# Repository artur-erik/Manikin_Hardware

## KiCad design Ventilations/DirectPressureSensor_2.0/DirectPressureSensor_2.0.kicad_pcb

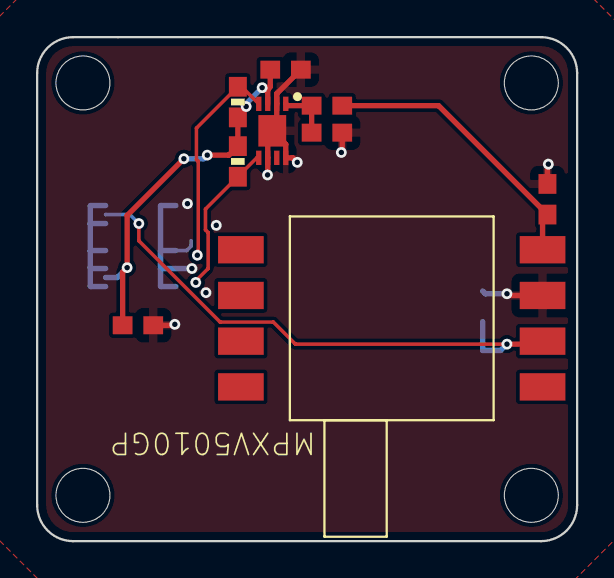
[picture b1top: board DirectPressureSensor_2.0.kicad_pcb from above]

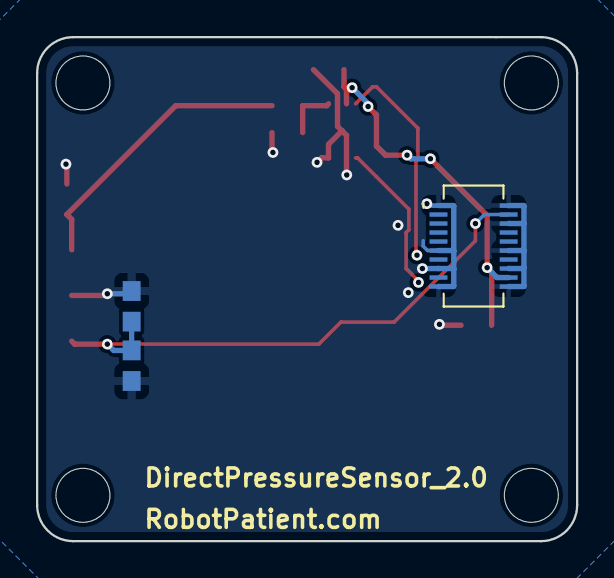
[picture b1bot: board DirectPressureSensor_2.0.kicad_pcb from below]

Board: 2 copper layers, 30.0 x 28.0 mm, 13 parts (3 on the bottom side), 7 nets.

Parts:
C1: 0.1uF; 0603_510
C2: 10uF; 0603_510
C3: 1.0uF; 0603_510
C4: 10nF; 0603_510
C5: 470pF; 0603_510
IC2: MCP3426A0-E_MC; SON50P300X200X100-9N
J5: 658511223020; J_Wurth_WR-BTB_658511223020
R1: 10K 0.1%; 0603_510
R2: 15K 0.1%; 0603_510
R28, R29: 4.7K; 0603-RES
U$3: MPXV5010GP; PRESSURE_SENSOR
U$40: ROBOTPATIENT_SMALL_MODULEBOARD; RP_SMALL_SENSOR_OUTLINE

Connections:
3.3V: C1.1, C2.1, IC2.3 (VDD), J5.19, R28.2, R29.2
5V: C3.2, C4.2, J5.12, U$3.2 (VS)
/Microcontroller/SCL: IC2.5 (SCL), R29.1
/Microcontroller/SDA: IC2.4 (SDA), R28.1
A0_PRESSURE_3.3V: IC2.1 (CH1+), R1.1, R2.2
A0_PRESSURE_5V: C5.2, R1.2, U$3.4 (VOUT)
GND: C1.2, C2.2, C3.1, C4.1, C5.1, IC2.2 (CH1-), IC2.6 (VSS), IC2.8 (CH2-), IC2.9 (EP), J5.1, J5.6, J5.8, J5.10, J5.11, J5.13, J5.16, J5.18, J5.20, R2.1, U$3.3 (GND)

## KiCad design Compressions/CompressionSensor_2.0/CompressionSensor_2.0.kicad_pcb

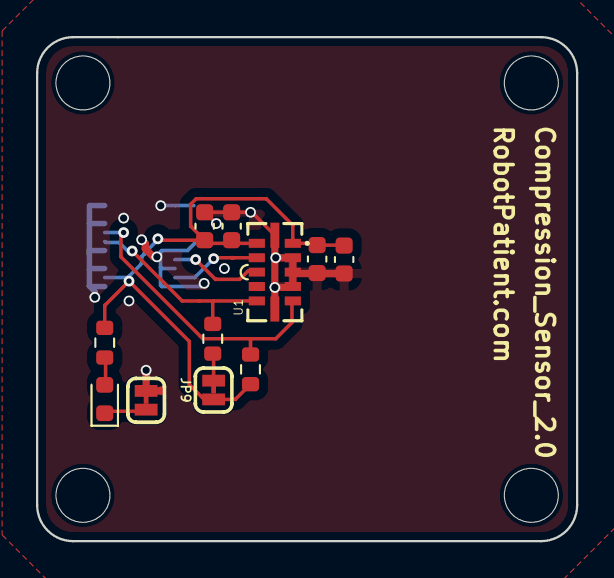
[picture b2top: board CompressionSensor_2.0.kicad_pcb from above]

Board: 2 copper layers, 30.0 x 28.0 mm, 13 parts (1 on the bottom side), 5 nets.

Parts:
C1: 4.7uF; C_0603_1608Metric
C2, C3: 10uF; C_0603_1608Metric
C4: 0.1uF; C_0603_1608Metric
D2: LED; LED_0603_1608Metric
J5: 658511223020; J_Wurth_WR-BTB_658511223020
JP9: INT; SMT-JUMPER_2_NC_TRACE_SILK
PWR0: INT; SMT-JUMPER_2_NC_TRACE_SILK
R1, R2: 10k; R_0603_1608Metric
R3: 1k; R_0603_1608Metric
U1: VL53L4CD
U$40: ROBOTPATIENT_SMALL_MODULEBOARD; RP_SMALL_SENSOR_OUTLINE

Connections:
3.3V: C1.1, C2.1, C3.1, C4.1, J5.19, JP9.2, R2.2, R3.2, U1.1, U1.11
/~INT: J5.15, R1.1
/~SHUT: J5.14, R2.1
GND: C1.2, C2.2, C3.2, C4.2, J5.1, J5.6, J5.8, J5.10, J5.11, J5.13, J5.16, J5.18, J5.20, PWR0.1, U1.2, U1.3, U1.4, U1.6, U1.12
unnamed: D2.2 (A), R3.1

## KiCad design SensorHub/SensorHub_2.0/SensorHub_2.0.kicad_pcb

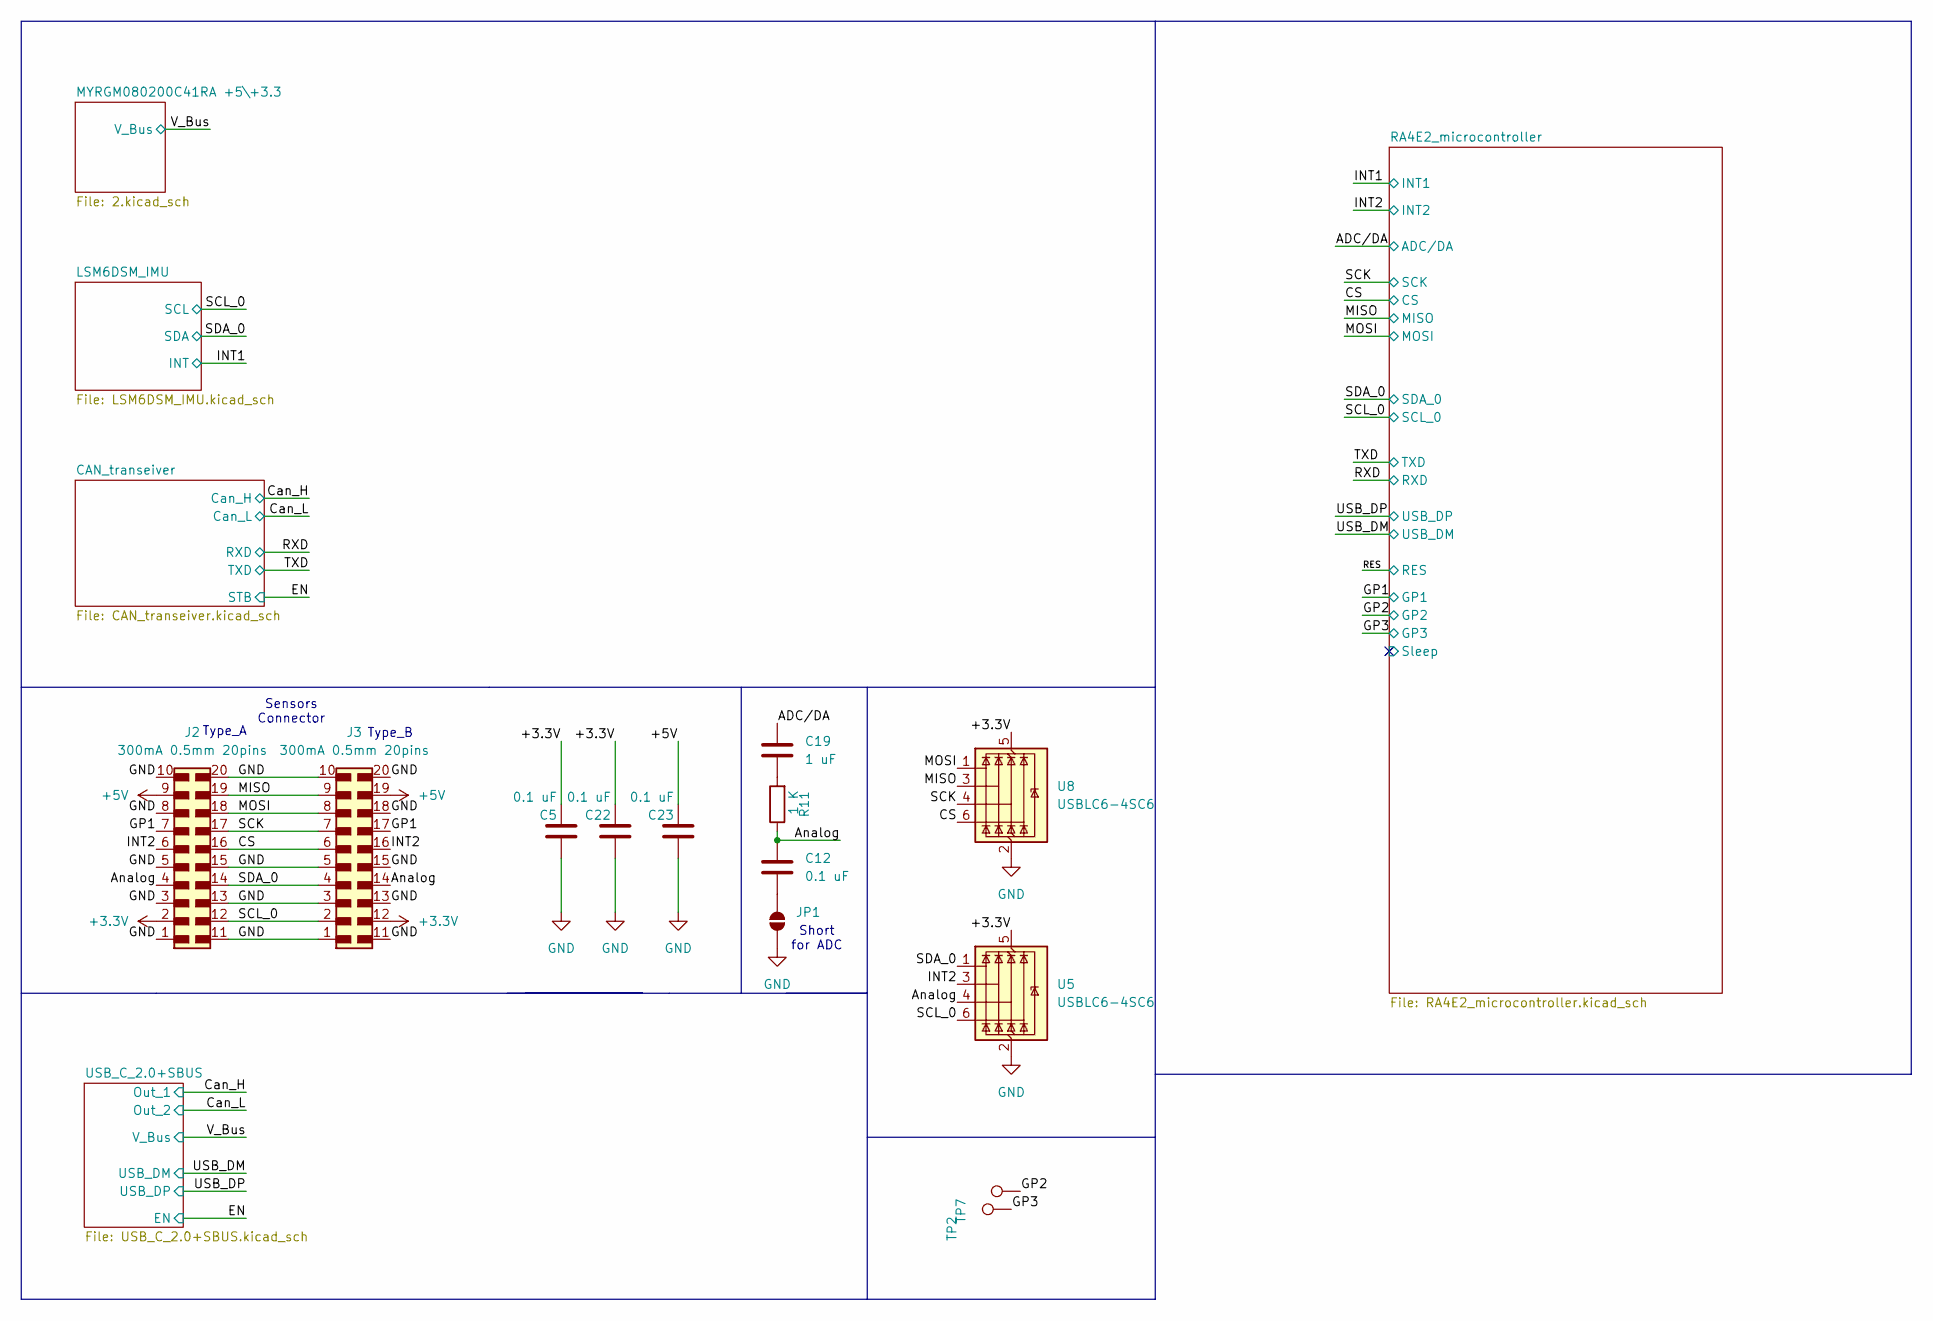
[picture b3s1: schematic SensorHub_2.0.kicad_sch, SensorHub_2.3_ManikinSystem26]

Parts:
C5, C12, C22, C23: 0.1 uF; C_0603_1608Metric
C19: 1 uF; C_0603_1608Metric
J2, J3: 658561423020; J_Wurth_WR-BTB_658561423020; Part Number 658561423020
JP1: SolderJumper_2_Open; SolderJumper-2_P1.3mm_Open_RoundedPad1.0x1.5mm
R11: 1 K; R_0603_1608Metric
TP2, TP7: TestPoint; TestPoint_Pad_1.0x1.0mm
U5, U8: USBLC6-4SC6; SOT-23-6; MPN USBLC6-4SC6Y

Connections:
+3.3V: C5.1, C22.1, J2.2, J3.12, U5.5 (VBUS), U8.5 (VBUS); also elsewhere on the board
+5V: C23.1, J2.9, J3.19; also elsewhere on the board
/ADC/DA: C19.1; also elsewhere on the board
/Analog: C12.1, J2.4, J3.14, R11.1, U5.4 (I/O3)
/CS: J2.16, J3.6, U8.6 (I/O4); also elsewhere on the board
/GP1: J2.7, J3.17; also elsewhere on the board
/GP2: TP7.1; also elsewhere on the board
/GP3: TP2.1; also elsewhere on the board
/INT2: J2.6, J3.16, U5.3 (I/O2); also elsewhere on the board
/MISO: J2.19, J3.9, U8.3 (I/O2); also elsewhere on the board
/MOSI: J2.18, J3.8, U8.1 (I/O1); also elsewhere on the board
/SCK: J2.17, J3.7, U8.4 (I/O3); also elsewhere on the board
/SCL_0: J2.12, J3.2, U5.6 (I/O4); also elsewhere on the board
/SDA_0: J2.14, J3.4, U5.1 (I/O1); also elsewhere on the board
GND: C5.2, C22.2, C23.2, J2.1, J2.3, J2.5, J2.8, J2.10, J2.11, J2.13, J2.15, J2.20, J3.1, J3.3, J3.5, J3.10, J3.11, J3.13, J3.15, J3.18, J3.20, JP1.1 (A), U5.2 (GND), U8.2 (GND); also elsewhere on the board
unnamed: C19.2, R11.2
unnamed: C12.2, JP1.2 (B)

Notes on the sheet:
Type_A
Sensors Connector
Type_B
Short for ADC

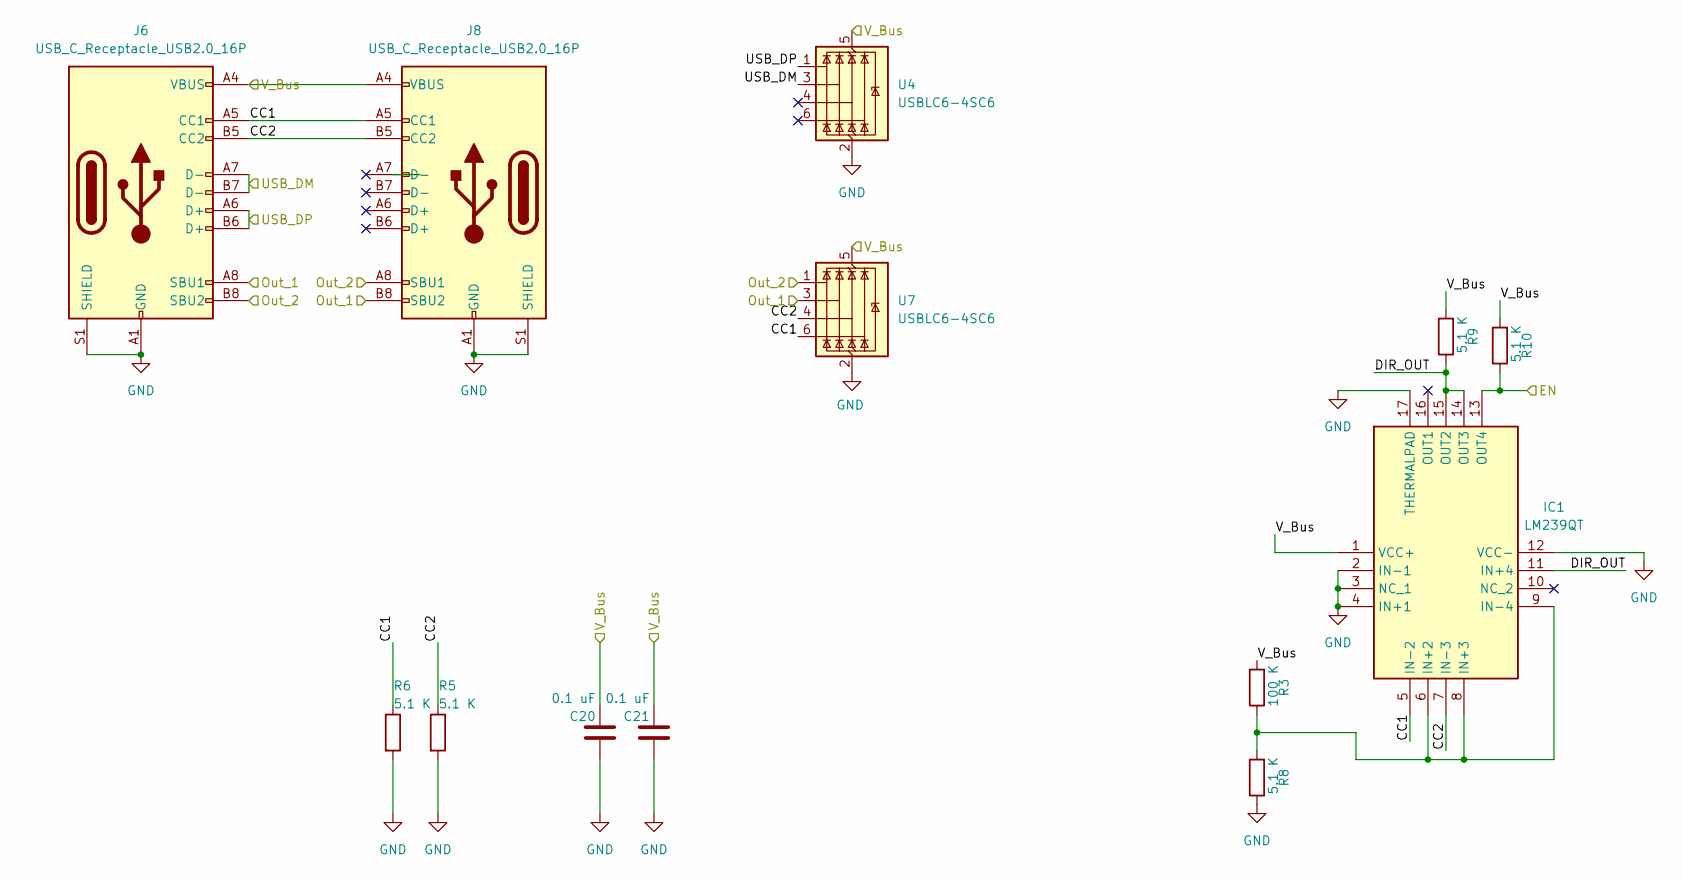
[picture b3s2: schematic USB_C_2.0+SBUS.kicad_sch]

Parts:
C20, C21: 0.1 uF; C_0603_1608Metric
IC1: LM239QT; QFN50P300X300X100-17N; Mouser Part Number 511-LM239QT
J6, J8: USB_C_Receptacle_USB2.0_16P; USB_C_Receptacle_Palconn_UTC16-G
R3: 100 K; R_0603_1608Metric
R5, R6, R8, R9, R10: 5.1 K; R_0603_1608Metric
U4, U7: USBLC6-4SC6; SOT-23-6; MPN USBLC6-4SC6Y

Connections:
/Can_H: J6.A8 (SBU1), J8.B8 (SBU2), U7.3 (I/O2); also elsewhere on the board
/Can_L: J6.B8 (SBU2), J8.A8 (SBU1), U7.1 (I/O1); also elsewhere on the board
/EN: IC1.13 (OUT4), R10.1; also elsewhere on the board
/USB_C_2.0+SBUS/CC1: IC1.5 (IN-2), J6.A5 (CC1), J8.A5 (CC1), R6.1, U7.6 (I/O4)
/USB_C_2.0+SBUS/CC2: IC1.7 (IN-3), J6.B5 (CC2), J8.B5 (CC2), R5.1, U7.4 (I/O3)
/USB_C_2.0+SBUS/DIR_OUT: IC1.11 (IN+4), IC1.14 (OUT3), IC1.15 (OUT2), R9.1
/USB_DM: J6.A7 (D-), J6.B7 (D-), U4.3 (I/O2); also elsewhere on the board
/USB_DP: J6.A6 (D+), J6.B6 (D+), U4.1 (I/O1); also elsewhere on the board
/V_Bus: C20.1, C21.1, IC1.1 (VCC+), J6.A4 (VBUS), J6.A9 (VBUS), J6.B4 (VBUS), J6.B9 (VBUS), J8.A4 (VBUS), J8.A9 (VBUS), J8.B4 (VBUS), J8.B9 (VBUS), R3.2, R9.2, R10.2, U4.5 (VBUS), U7.5 (VBUS); also elsewhere on the board
GND: C20.2, C21.2, IC1.2 (IN-1), IC1.3 (NC_1), IC1.4 (IN+1), IC1.12 (VCC-), IC1.17 (THERMALPAD), J6.A1 (GND), J6.A12 (GND), J6.B1 (GND), J6.B12 (GND), J6.S1 (SHIELD), J8.A1 (GND), J8.A12 (GND), J8.B1 (GND), J8.B12 (GND), J8.S1 (SHIELD), R5.2, R6.2, R8.1, U4.2 (GND), U7.2 (GND); also elsewhere on the board
unnamed: IC1.6 (IN+2), IC1.8 (IN+3), IC1.9 (IN-4), R3.1, R8.2

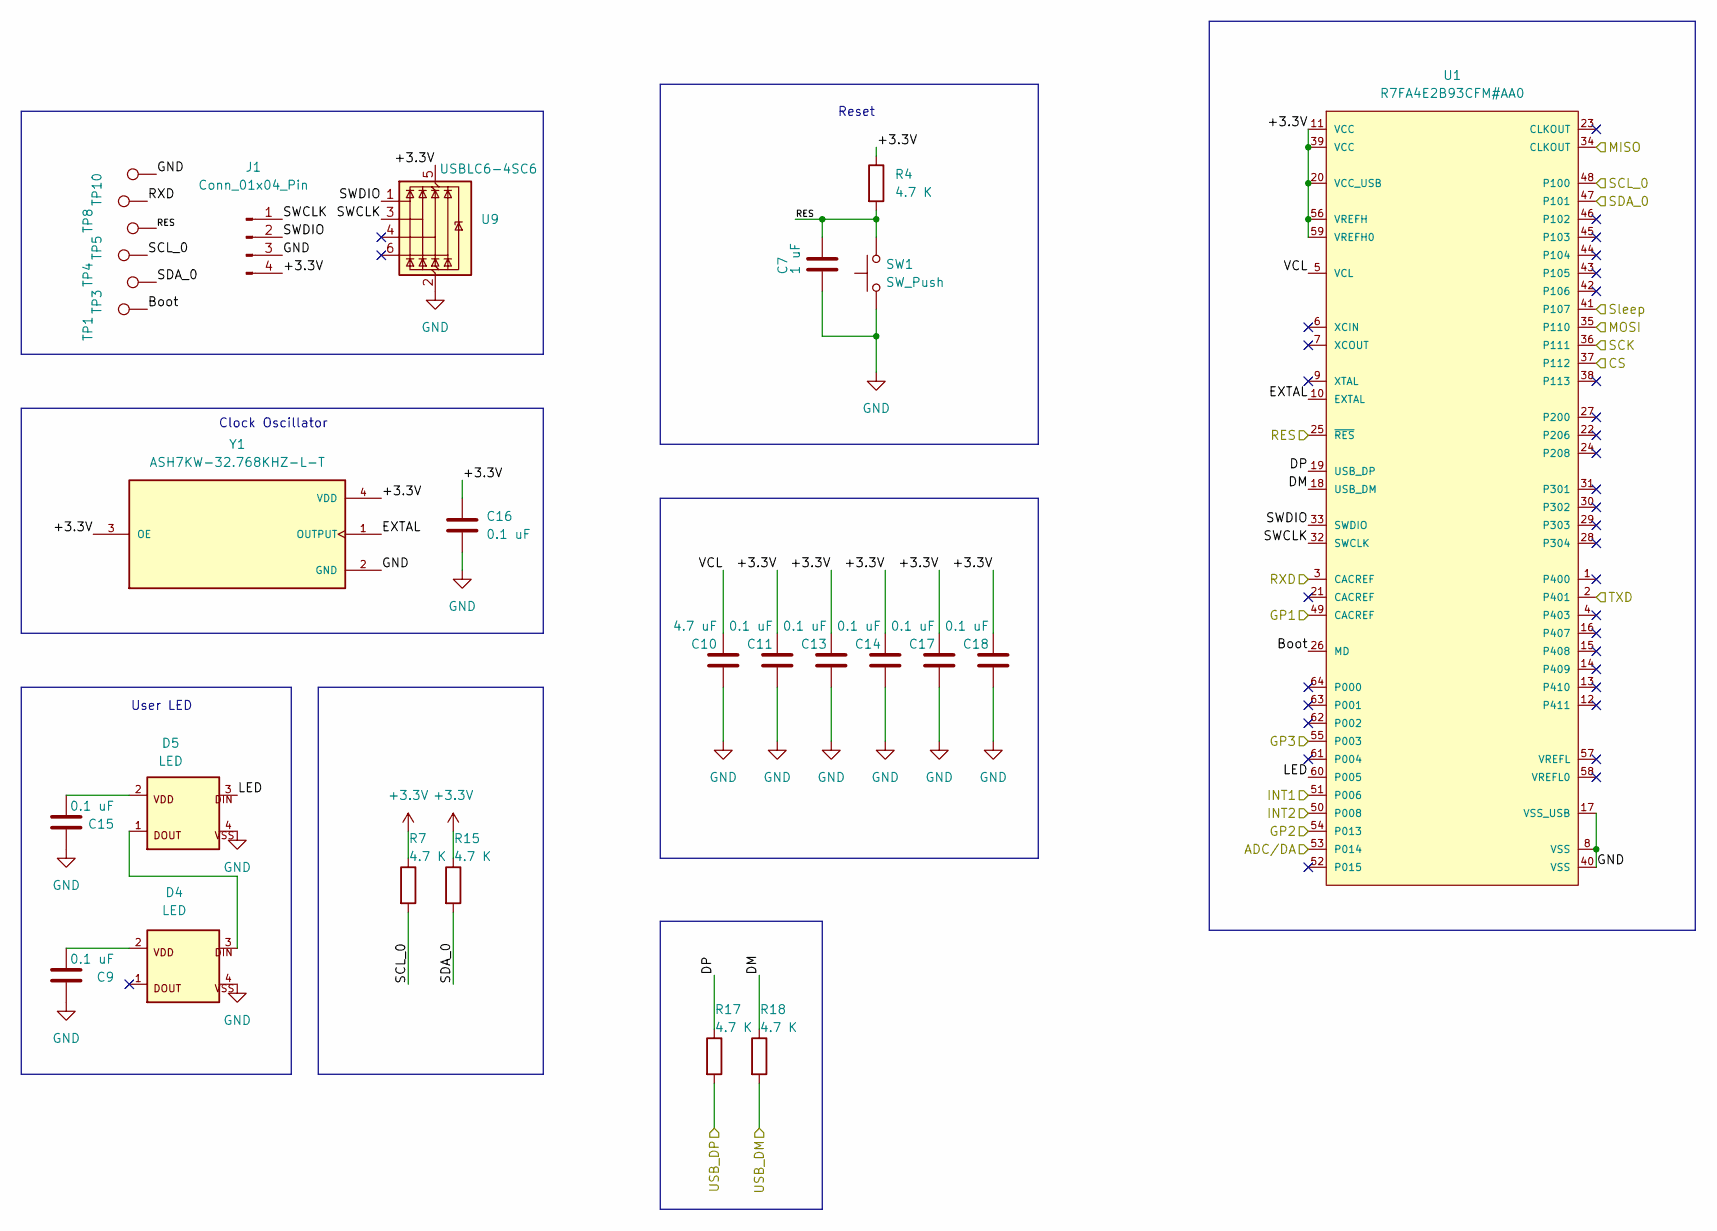
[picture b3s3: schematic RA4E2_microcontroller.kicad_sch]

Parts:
C7: 1 uF; C_0603_1608Metric
C9, C11, C13, C14, C15, C16, C17, C18: 0.1 uF; C_0603_1608Metric
C10: 4.7 uF; C_0603_1608Metric
D4, D5: LED; 1312020030000; MPN 1312020030000
J1: Conn_01x04_Pin; PinHeader_1x04_P1.27mm_Vertical
R4, R7, R15, R17, R18: 4.7 K; R_0603_1608Metric
SW1: SW_Push; B3U-1000P(M)-B; MPN B3U-1000PM-B
TP1, TP3, TP4, TP5, TP8, TP10: TestPoint; TestPoint_Pad_1.0x1.0mm
U1: R7FA4E2B93CFM#AA0; Renesas-PLQP0064KB-C-0-0-IPC_A; MPN R7FA4E2B93CFM#AA0
U9: USBLC6-4SC6; SOT-23-6; MPN USBLC6-4SC6Y
Y1: ASH7KW-32.768KHZ-L-T; XTAL_ASH7KW-32.768KHZ-L-T; PARTREV 07.07.2021

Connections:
+3.3V: C11.1, C13.1, C14.1, C16.1, C17.1, C18.1, J1.4, R4.1, R7.1, R15.1, U1.11 (VCC), U1.20 (VCC_USB), U1.39 (VCC), U1.56 (VREFH), U1.59 (VREFH0), U9.5 (VBUS), Y1.3 (OE), Y1.4 (VDD); also elsewhere on the board
/ADC/DA: U1.53 (P014); also elsewhere on the board
/CS: U1.37 (P112); also elsewhere on the board
/GP1: U1.49 (CACREF); also elsewhere on the board
/GP2: U1.54 (P013); also elsewhere on the board
/GP3: U1.55 (P003); also elsewhere on the board
/INT1: U1.51 (P006); also elsewhere on the board
/INT2: U1.50 (P008); also elsewhere on the board
/MISO: U1.34 (CLKOUT); also elsewhere on the board
/MOSI: U1.35 (P110); also elsewhere on the board
/RA4E2_microcontroller/Boot: TP1.1, U1.26 (MD)
/RA4E2_microcontroller/DM: R18.1, U1.18 (USB_DM)
/RA4E2_microcontroller/DP: R17.1, U1.19 (USB_DP)
/RA4E2_microcontroller/EXTAL: U1.10 (EXTAL), Y1.1 (OUTPUT)
/RA4E2_microcontroller/LED: D5.3, U1.60 (P005)
/RA4E2_microcontroller/SWCLK: J1.1, U1.32 (SWCLK), U9.3 (I/O2)
/RA4E2_microcontroller/SWDIO: J1.2, U1.33 (SWDIO), U9.1 (I/O1)
/RA4E2_microcontroller/Sleep: U1.41 (P107)
/RA4E2_microcontroller/VCL: C10.1, U1.5 (VCL)
/RES: C7.1, R4.2, SW1.2, TP5.1, U1.25 (~RES)
/RXD: TP8.1, U1.3 (CACREF); also elsewhere on the board
/SCK: U1.36 (P111); also elsewhere on the board
/SCL_0: R7.2, TP4.1, U1.48 (P100); also elsewhere on the board
/SDA_0: R15.2, TP3.1, U1.47 (P101); also elsewhere on the board
/TXD: U1.2 (P401); also elsewhere on the board
/USB_DM: R18.2; also elsewhere on the board
/USB_DP: R17.2; also elsewhere on the board
GND: C7.2, C9.2, C10.2, C11.2, C13.2, C14.2, C15.2, C16.2, C17.2, C18.2, D4.4, D5.4, J1.3, SW1.1, TP10.1, U1.8 (VSS), U1.17 (VSS_USB), U1.40 (VSS), U9.2 (GND), Y1.2 (GND); also elsewhere on the board
unnamed: C9.1, D4.2
unnamed: C15.1, D5.2
unnamed: D4.3, D5.1

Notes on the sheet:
User LED
Clock Oscillator
Reset

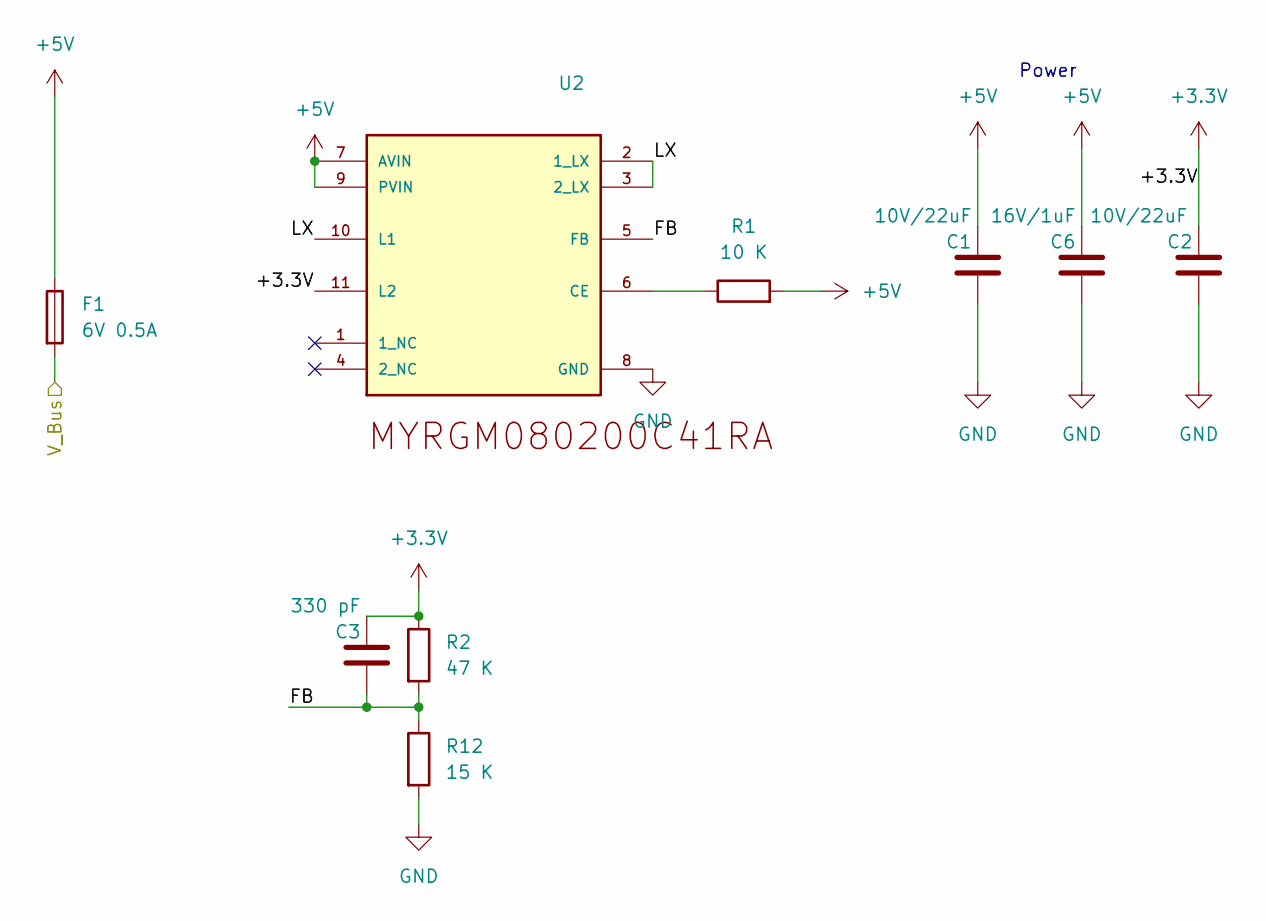
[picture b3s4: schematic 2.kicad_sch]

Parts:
C1, C2: 10V/22uF; C_0603_1608Metric
C3: 330 pF; C_0603_1608Metric
C6: 16V/1uF; C_0603_1608Metric
F1: 6V 0.5A; Fuse_1206_3216Metric_Pad1.42x1.75mm_HandSolder; MPN SMD1206B050TF
R1: 10 K; R_0603_1608Metric
R2: 47 K; R_0603_1608Metric
R12: 15 K; R_0603_1608Metric
U2: MYRGM080200C41RA; MURATA_MYRGM080200C41RA_0; MOUSER_PART_NUMBER 81-MYRGM080200C41RA

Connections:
+3.3V: C2.1, C3.1, R2.1, U2.11 (L2); also elsewhere on the board
+5V: C1.1, C6.1, F1.1, R1.2, U2.7 (AVIN), U2.9 (PVIN); also elsewhere on the board
/MYRGM080200C41RA +5\+3.3/FB: C3.2, R2.2, R12.1, U2.5 (FB)
/MYRGM080200C41RA +5\+3.3/LX: U2.2 (1_LX), U2.3 (2_LX), U2.10 (L1)
/V_Bus: F1.2; also elsewhere on the board
GND: C1.2, C2.2, C6.2, R12.2, U2.8 (GND); also elsewhere on the board
unnamed: R1.1, U2.6 (CE)

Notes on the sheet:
Power

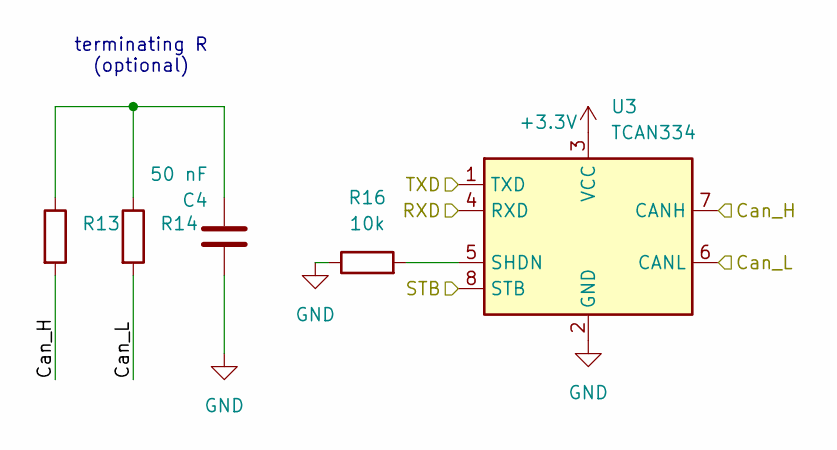
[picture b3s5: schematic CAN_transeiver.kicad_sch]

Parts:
C4: 50 nF; C_0603_1608Metric
R13, R14: R_0603_1608Metric
R16: 10k; R_0603_1608Metric
U3: TCAN334; TSOT-23-8; MPN TCAN334GDCNT

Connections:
+3.3V: U3.3 (VCC); also elsewhere on the board
/Can_H: R13.2, U3.7 (CANH); also elsewhere on the board
/Can_L: R14.2, U3.6 (CANL); also elsewhere on the board
/EN: U3.8 (STB); also elsewhere on the board
/RXD: U3.4 (RXD); also elsewhere on the board
/TXD: U3.1 (TXD); also elsewhere on the board
GND: C4.2, R16.1, U3.2 (GND); also elsewhere on the board
unnamed: C4.1, R13.1, R14.1
unnamed: R16.2, U3.5 (SHDN)

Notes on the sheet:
terminating R (optional)

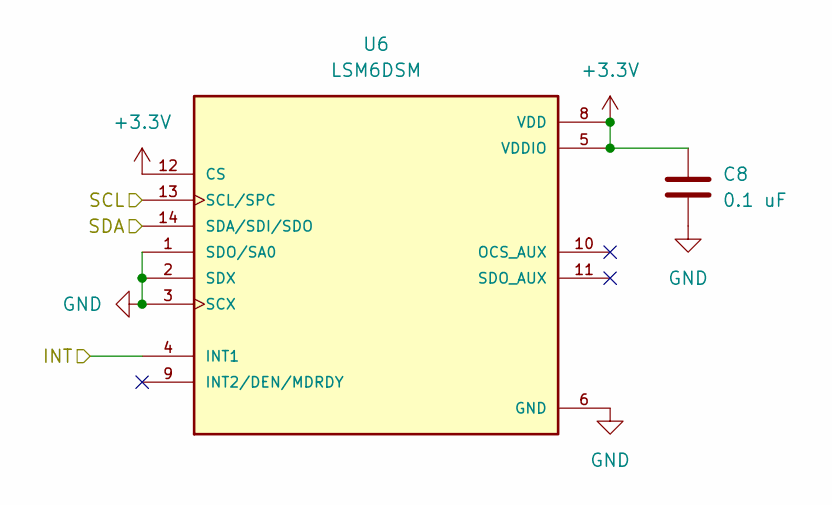
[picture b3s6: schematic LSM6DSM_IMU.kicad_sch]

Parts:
C8: 0.1 uF; C_0603_1608Metric
U6: LSM6DSM; PQFN50P300X250X86-14N; PARTREV Rev 7

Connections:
+3.3V: C8.1, U6.5 (VDDIO), U6.8 (VDD), U6.12 (CS); also elsewhere on the board
/INT1: U6.4 (INT1); also elsewhere on the board
/SCL_0: U6.13 (SCL/SPC); also elsewhere on the board
/SDA_0: U6.14 (SDA/SDI/SDO); also elsewhere on the board
GND: C8.2, U6.1 (SDO/SA0), U6.2 (SDX), U6.3 (SCX), U6.6 (GND), U6.7 (GND); also elsewhere on the board

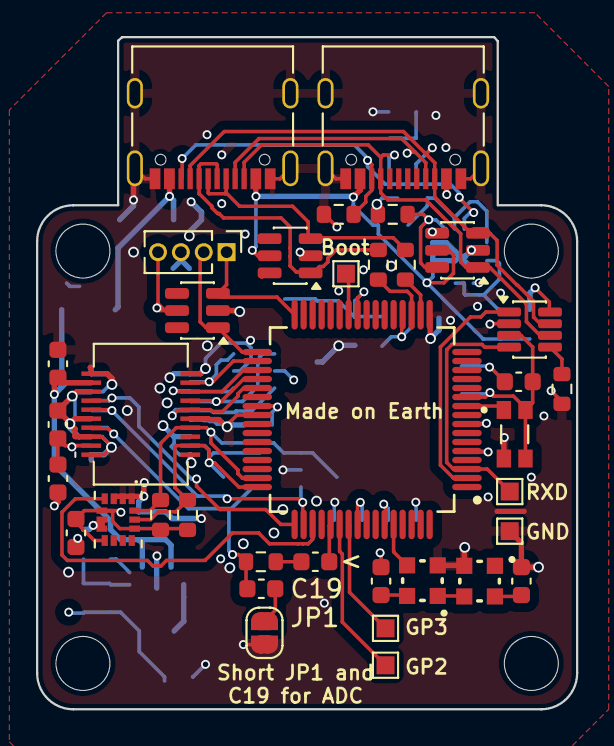
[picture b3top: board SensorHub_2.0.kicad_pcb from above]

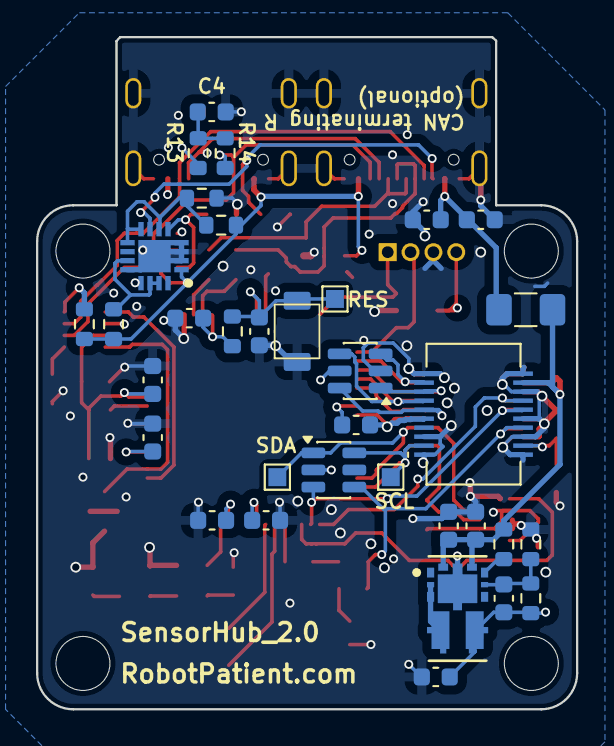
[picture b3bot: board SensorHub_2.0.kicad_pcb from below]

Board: 4 copper layers, 30.0 x 37.3 mm, 71 parts (34 on the bottom side), 47 nets.

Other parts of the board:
U$40: ROBOTPATIENT_SMALL_MODULEBOARD; RP_SMALL_SENSOR_OUTLINE

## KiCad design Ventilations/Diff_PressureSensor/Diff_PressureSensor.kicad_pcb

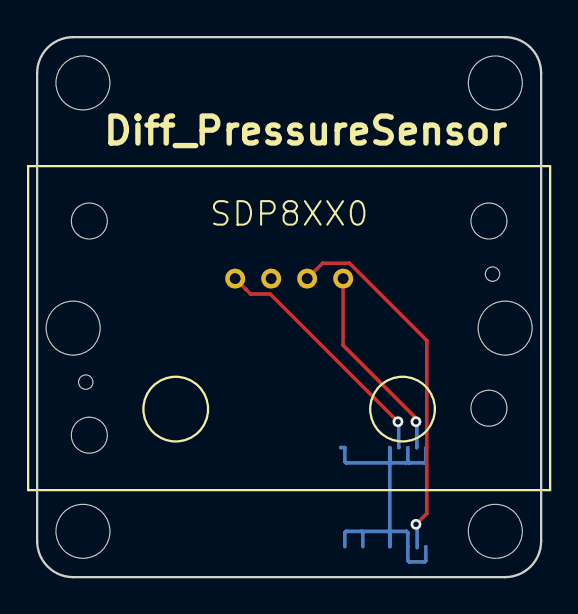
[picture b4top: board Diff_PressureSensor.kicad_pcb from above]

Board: 2 copper layers, 28.0 x 30.0 mm, 3 parts (1 on the bottom side), 4 nets.

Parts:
J3: 658561423020; J_Wurth_WR-BTB_658561423020
SDP8XX0: SDPXXX
U2: ROBOTPATIENT_SMALL_MODULEBOARD; RP_SMALL_SENSOR_OUTLINE

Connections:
/3.3V: J3.12, SDP8XX0.P3_VCC (P2_VDD)
/GND: J3.1, J3.3, J3.5, J3.10, J3.11, J3.13, J3.15, J3.18, J3.20, SDP8XX0.P2_GND (P3_GND)
/SCL: J3.2, SDP8XX0.P4_CLK (P1_SCL)
/SDA: J3.4, SDP8XX0.P1_SDA (P4_SDA)

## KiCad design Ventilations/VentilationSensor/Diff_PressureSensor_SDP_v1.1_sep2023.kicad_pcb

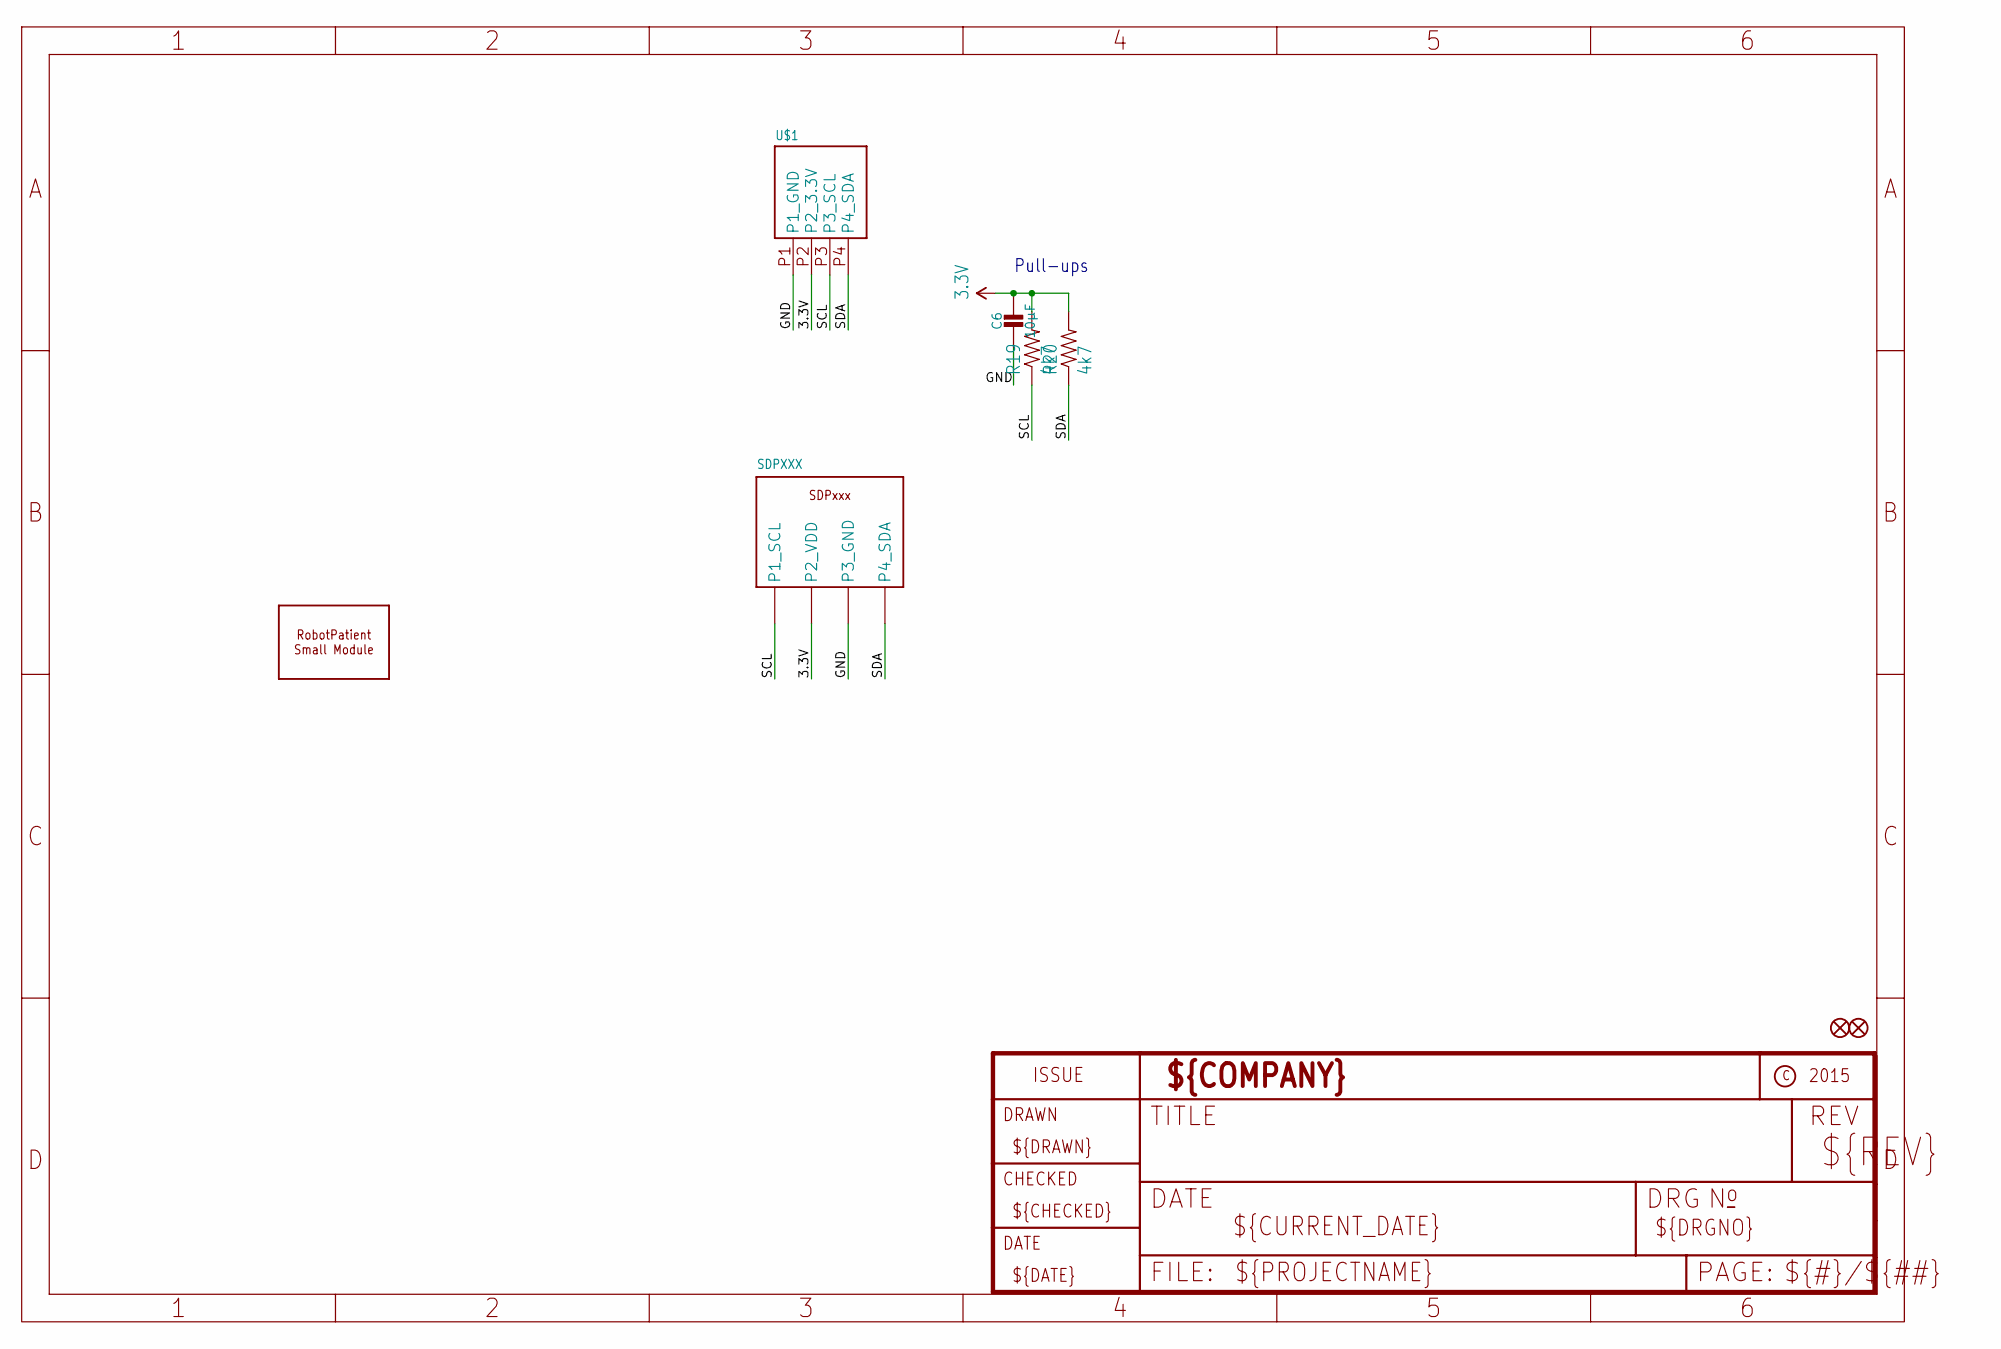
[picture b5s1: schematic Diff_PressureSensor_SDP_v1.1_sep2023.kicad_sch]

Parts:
C6: 10µF; 0805-NO
FID1, FID2: FIDUCIAL""; FIDUCIAL_1MM
R19, R20: 4k7; 0603-RES
SDP8XX0: SDPXXX
U$1: PHOENIX_PTSM_M4_THANGLE; PTSM_M4_TH
U$2: ROBOTPATIENT_SMALL_MODULEBOARD; RP_SMALL_SENSOR_OUTLINE

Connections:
3.3V: C6.1, R19.2, R20.2, SDP8XX0.P3_VCC (P2_VDD), U$1.P2 (P2_3.3V)
GND: C6.2, SDP8XX0.P2_GND (P3_GND), U$1.P1 (P1_GND)
SCL: R19.1, SDP8XX0.P4_CLK (P1_SCL), U$1.P3 (P3_SCL)
SDA: R20.1, SDP8XX0.P1_SDA (P4_SDA), U$1.P4 (P4_SDA)

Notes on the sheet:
Pull-ups

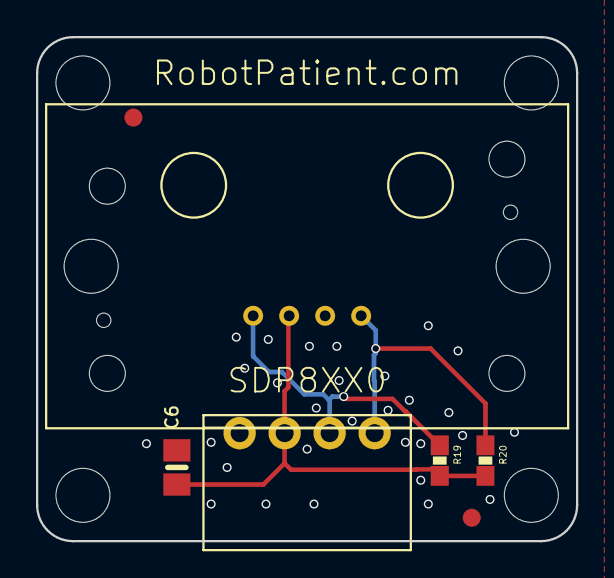
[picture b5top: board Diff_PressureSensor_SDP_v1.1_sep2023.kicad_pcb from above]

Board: 2 copper layers, 30.0 x 28.0 mm, 8 parts (0 on the bottom side), 4 nets.
